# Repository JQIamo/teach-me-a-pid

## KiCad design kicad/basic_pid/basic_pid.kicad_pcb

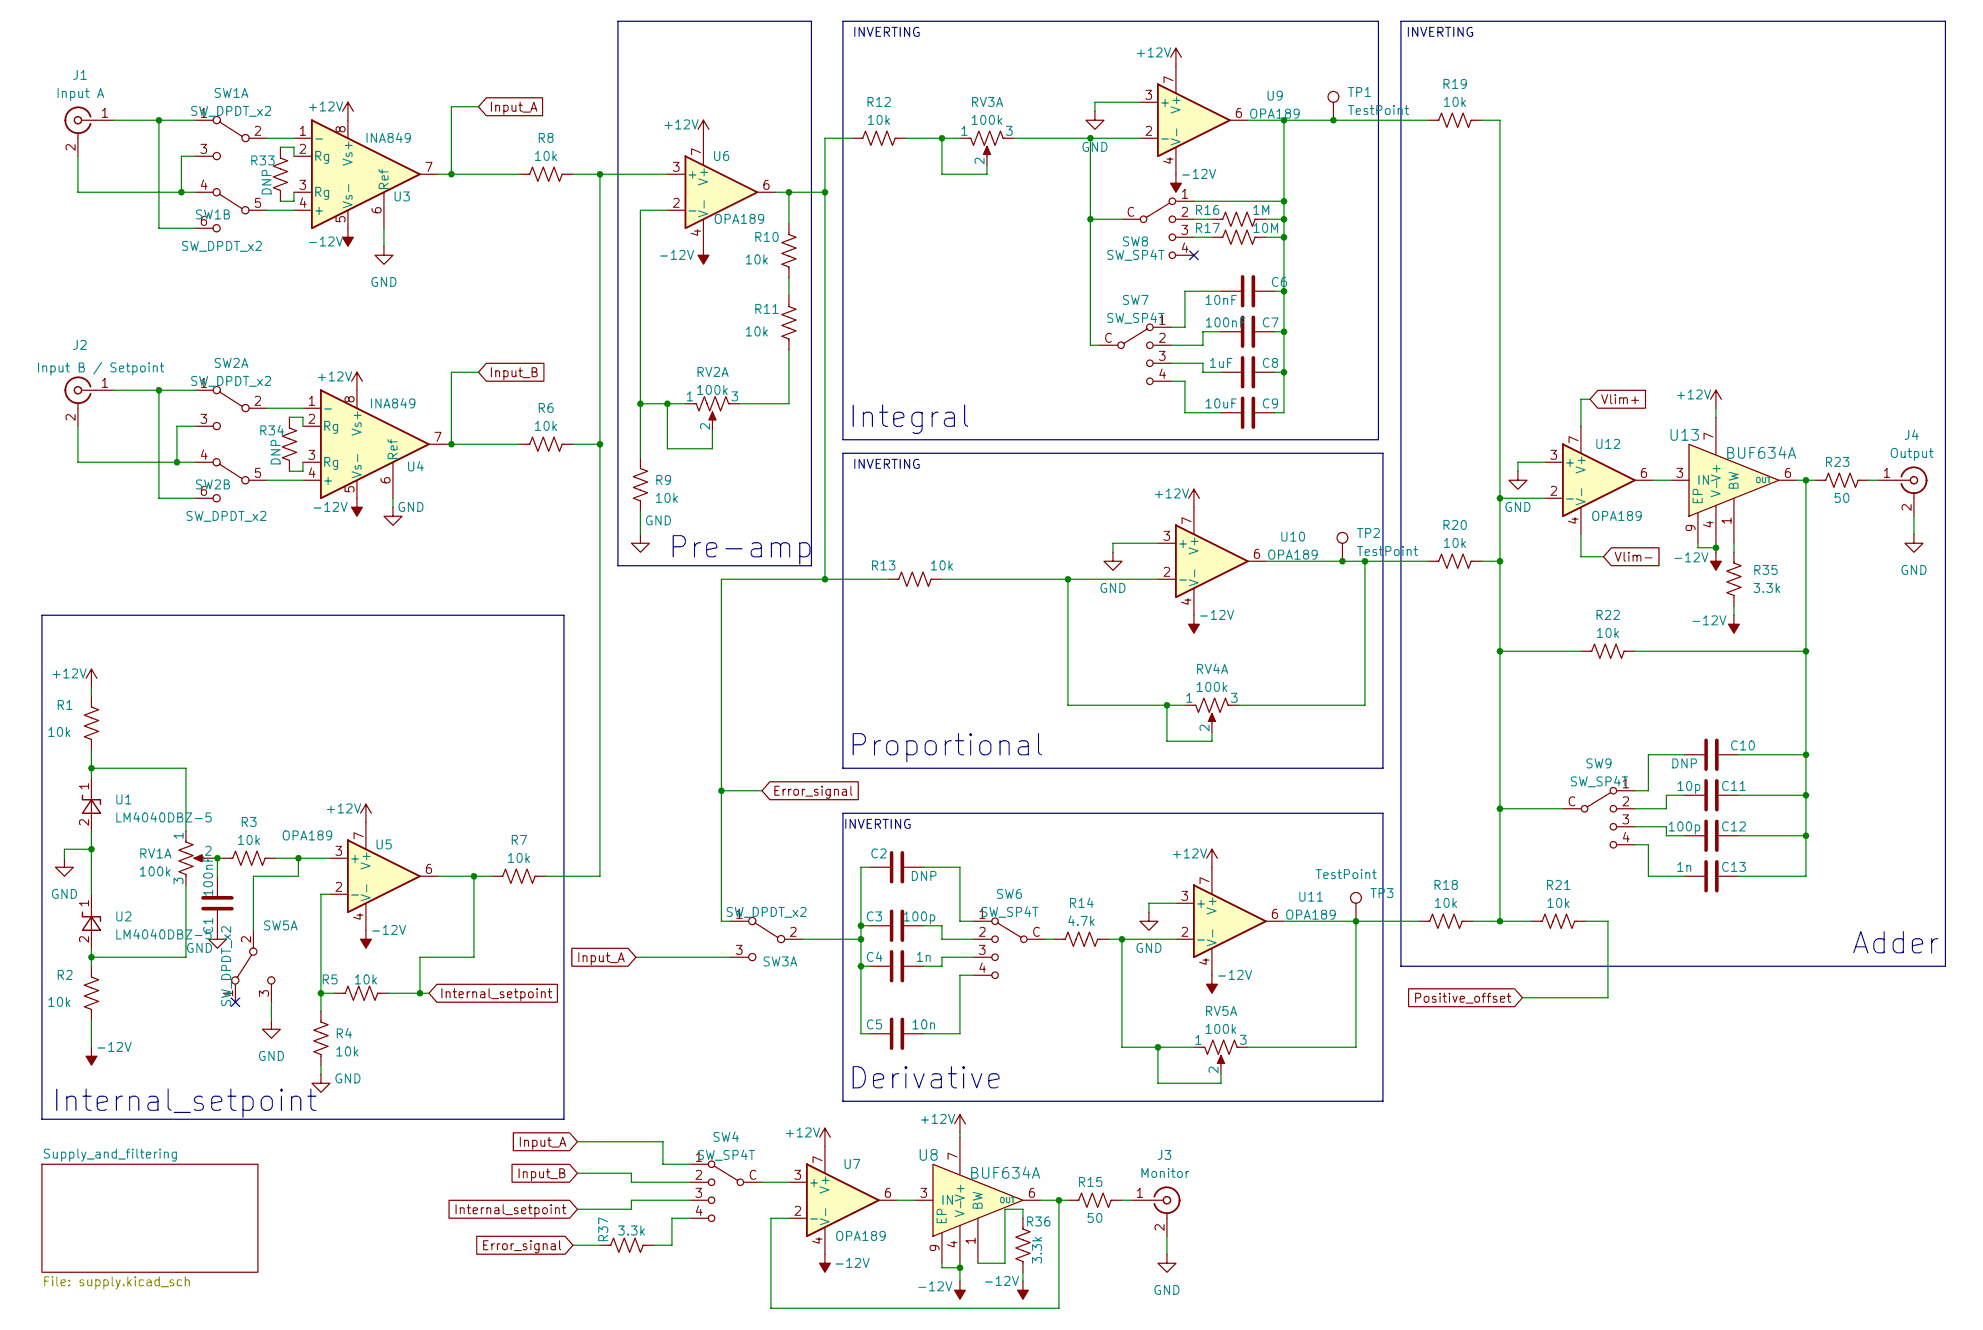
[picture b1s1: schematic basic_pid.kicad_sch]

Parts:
C1, C7: 100nF; C_0805_2012Metric
C2, C10: DNP; C_0805_2012Metric
C3, C12: 100p; C_0805_2012Metric
C4, C13: 1n; C_0805_2012Metric
C5: 10n; C_0805_2012Metric
C6: 10nF; C_0805_2012Metric
C8: 1uF; C_0805_2012Metric
C9: 10uF; C_0805_2012Metric
C11: 10p; C_0805_2012Metric
J1: Input A; BNC_Amphenol_031-5539_Vertical
J2: Input B / Setpoint; BNC_Amphenol_031-5539_Vertical
J3: Monitor; BNC_Amphenol_031-5539_Vertical
J4: Output; BNC_Amphenol_031-5539_Vertical
R1, R2: 10k; R_0805_2012Metric
R3, R4, R5, R6, R7, R8, R9, R10, R11, R12, R13, R18, R19, R20, R21, R22: 10k; R_0805_2012Metric; DIGIKEY 2019-RN73H2ATTD1002B25CT-ND
R14: 4.7k; R_0805_2012Metric
R15, R23: 50; R_0805_2012Metric
R16: 1M; R_0805_2012Metric; PARTNO AC0805JR-071ML; DIGIKEY YAG3766CT-ND
R17: 10M; R_0805_2012Metric; PARTNO RC0805JR-0710ML; DIGIKEY 311-10MARCT-ND
R33, R34: DNP; R_0805_2012Metric; DIGIKEY 2019-RN73H2ATTD1002B25CT-ND
R35, R36, R37: 3.3k; R_0805_2012Metric; DIGIKEY 2019-RN73H2ATTD3301B25CT-ND
RV1, RV2, RV3, RV4, RV5: 100k; Slide_pot_45mm; PARTNO PTL45-15O0-104B1; DIGIKEY PTL45-15O0-104B1-ND
SW1, SW2, SW3, SW5: SW_DPDT_x2; MHS222; PARTNO 1825289-1; DIGIKEY 450-1572-ND
SW4, SW6, SW7, SW8, SW9: SW_SP4T; SLB1470; PARTNO SLB1470; DIGIKEY 679-2621-ND
TP1, TP2, TP3: TestPoint; TestPoint_Pad_D3.0mm
U1, U2: LM4040DBZ-5; SOT-23; PARTNO LM4040B50FTA; DIGIKEY LM4040B50FTADICT-ND
U3, U4: INA849; SOIC-8_3.9x4.9mm_P1.27mm; PARTNO INA849DR‎; DIGIKEY 296-INA849DRCT-ND‎
U5, U6, U7, U9, U10, U11, U12: OPA189; SOIC-8_3.9x4.9mm_P1.27mm; PARTNO OPA189ID; DIGIKEY 296-47522-ND
U8, U13: BUF634A; TI_SO-PowerPAD-8_ThermalVias; PARTNO BUF634AIDDAR; DIGIKEY 296-BUF634AIDDARCT-ND

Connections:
+12V: R1.2, U3.8 (Vs+), U4.8 (Vs+), U5.7 (V+), U6.7 (V+), U7.7 (V+), U8.7 (V+), U9.7 (V+), U10.7 (V+), U11.7 (V+), U13.7 (V+); also elsewhere on the board
-12V: R2.1, R35.1, R36.1, U3.5 (Vs-), U4.5 (Vs-), U5.4 (V-), U6.4 (V-), U7.4 (V-), U8.4 (V-), U8.9 (EP), U9.4 (V-), U10.4 (V-), U11.4 (V-), U13.4 (V-), U13.9 (EP); also elsewhere on the board
Error_signal: R10.2, R12.1, R13.1, R37.2, SW3.1 (A), U6.6
GND: C1.1, J3.2 (Ext), J4.2 (Ext), R4.1, R9.1, SW5.3 (C), U1.2 (A), U2.1 (K), U3.6 (Ref), U4.6 (Ref), U9.3 (+), U10.3 (+), U11.3 (+), U12.3 (+); also elsewhere on the board
Input_A: R8.1, SW3.3 (C), SW4.1, U3.7
Input_B: R6.1, SW4.2, U4.7
Internal_setpoint: R5.2, R7.1, SW4.3, U5.6
unnamed: C1.2, R3.1, RV1.2
unnamed: C2.2, SW6.1
unnamed: C3.2, SW6.2
unnamed: C4.2, SW6.3
unnamed: C5.2, SW6.4
unnamed: C6.1, C7.1, C8.1, C9.1, R16.2, R17.2, R19.1, SW8.1, TP1.1, U9.6
unnamed: C6.2, SW7.1
unnamed: C7.2, SW7.2
unnamed: C8.2, SW7.3
unnamed: C9.2, SW7.4
unnamed: C10.2, SW9.1
unnamed: C11.2, SW9.2
unnamed: C12.2, SW9.3
unnamed: C13.2, SW9.4
unnamed: J1.2 (Ext), SW1.3 (C), SW1.4 (A)
unnamed: J1.1 (In), SW1.1 (A), SW1.6 (C)
unnamed: J2.2 (Ext), SW2.3 (C), SW2.4 (A)
unnamed: J2.1 (In), SW2.1 (A), SW2.6 (C)
unnamed: J3.1 (In), R15.2
unnamed: J4.1 (In), R23.2
unnamed: R10.1, R11.2
unnamed: R11.1, RV2.3
unnamed: R12.2, RV3.1, RV3.2
unnamed: R16.1, SW8.2
unnamed: R17.1, SW8.3
unnamed: R18.1, RV5.3, TP3.1, U11.6
unnamed: R20.1, RV4.3, TP2.1, U10.6
unnamed: R33.1, U3.3 (Rg)
unnamed: R33.2, U3.2 (Rg)
unnamed: R34.1, U4.3 (Rg)
unnamed: R34.2, U4.2 (Rg)
unnamed: R37.1, SW4.4
unnamed: SW1.2 (B), U3.1 (-)
unnamed: SW1.5 (B), U3.4 (+)
unnamed: SW2.2 (B), U4.1 (-)
unnamed: SW2.5 (B), U4.4 (+)
unnamed: C2.1, C3.1, C4.1, C5.1, SW3.2 (B)
unnamed: SW4.C (Common), U7.3 (+)
unnamed: R3.2, SW5.2 (B), U5.3 (+)
unnamed: R14.1, SW6.C (Common)
unnamed: RV3.3, SW7.C (Common), SW8.C (Common), U9.2 (-)
unnamed: R18.2, R19.2, R20.2, R21.1, R22.1, SW9.C (Common), U12.2 (-)
unnamed: R1.1, RV1.1, U1.1 (K)
unnamed: R2.2, RV1.3, U2.2 (A)
unnamed: R4.2, R5.1, U5.2 (-)
unnamed: R6.2, R7.2, R8.2, U6.3 (+)
unnamed: R9.2, RV2.1, RV2.2, U6.2 (-)
unnamed: R15.1, U7.2 (-), U8.6 (OUT)
unnamed: R36.2, U8.1 (BW)
unnamed: U7.6, U8.3 (IN)
unnamed: R13.2, RV4.1, RV4.2, U10.2 (-)
unnamed: R14.2, RV5.1, RV5.2, U11.2 (-)
unnamed: R35.2, U13.1 (BW)
unnamed: U12.6, U13.3 (IN)
unnamed: C10.1, C11.1, C12.1, C13.1, R22.2, R23.1, U13.6 (OUT)
Positive_offset: R21.2; also elsewhere on the board
Vlim+: U12.7 (V+); also elsewhere on the board
Vlim-: U12.4 (V-); also elsewhere on the board

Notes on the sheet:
INVERTING
Pre-amp
Proportional
Adder
Derivative
Integral
Internal_setpoint

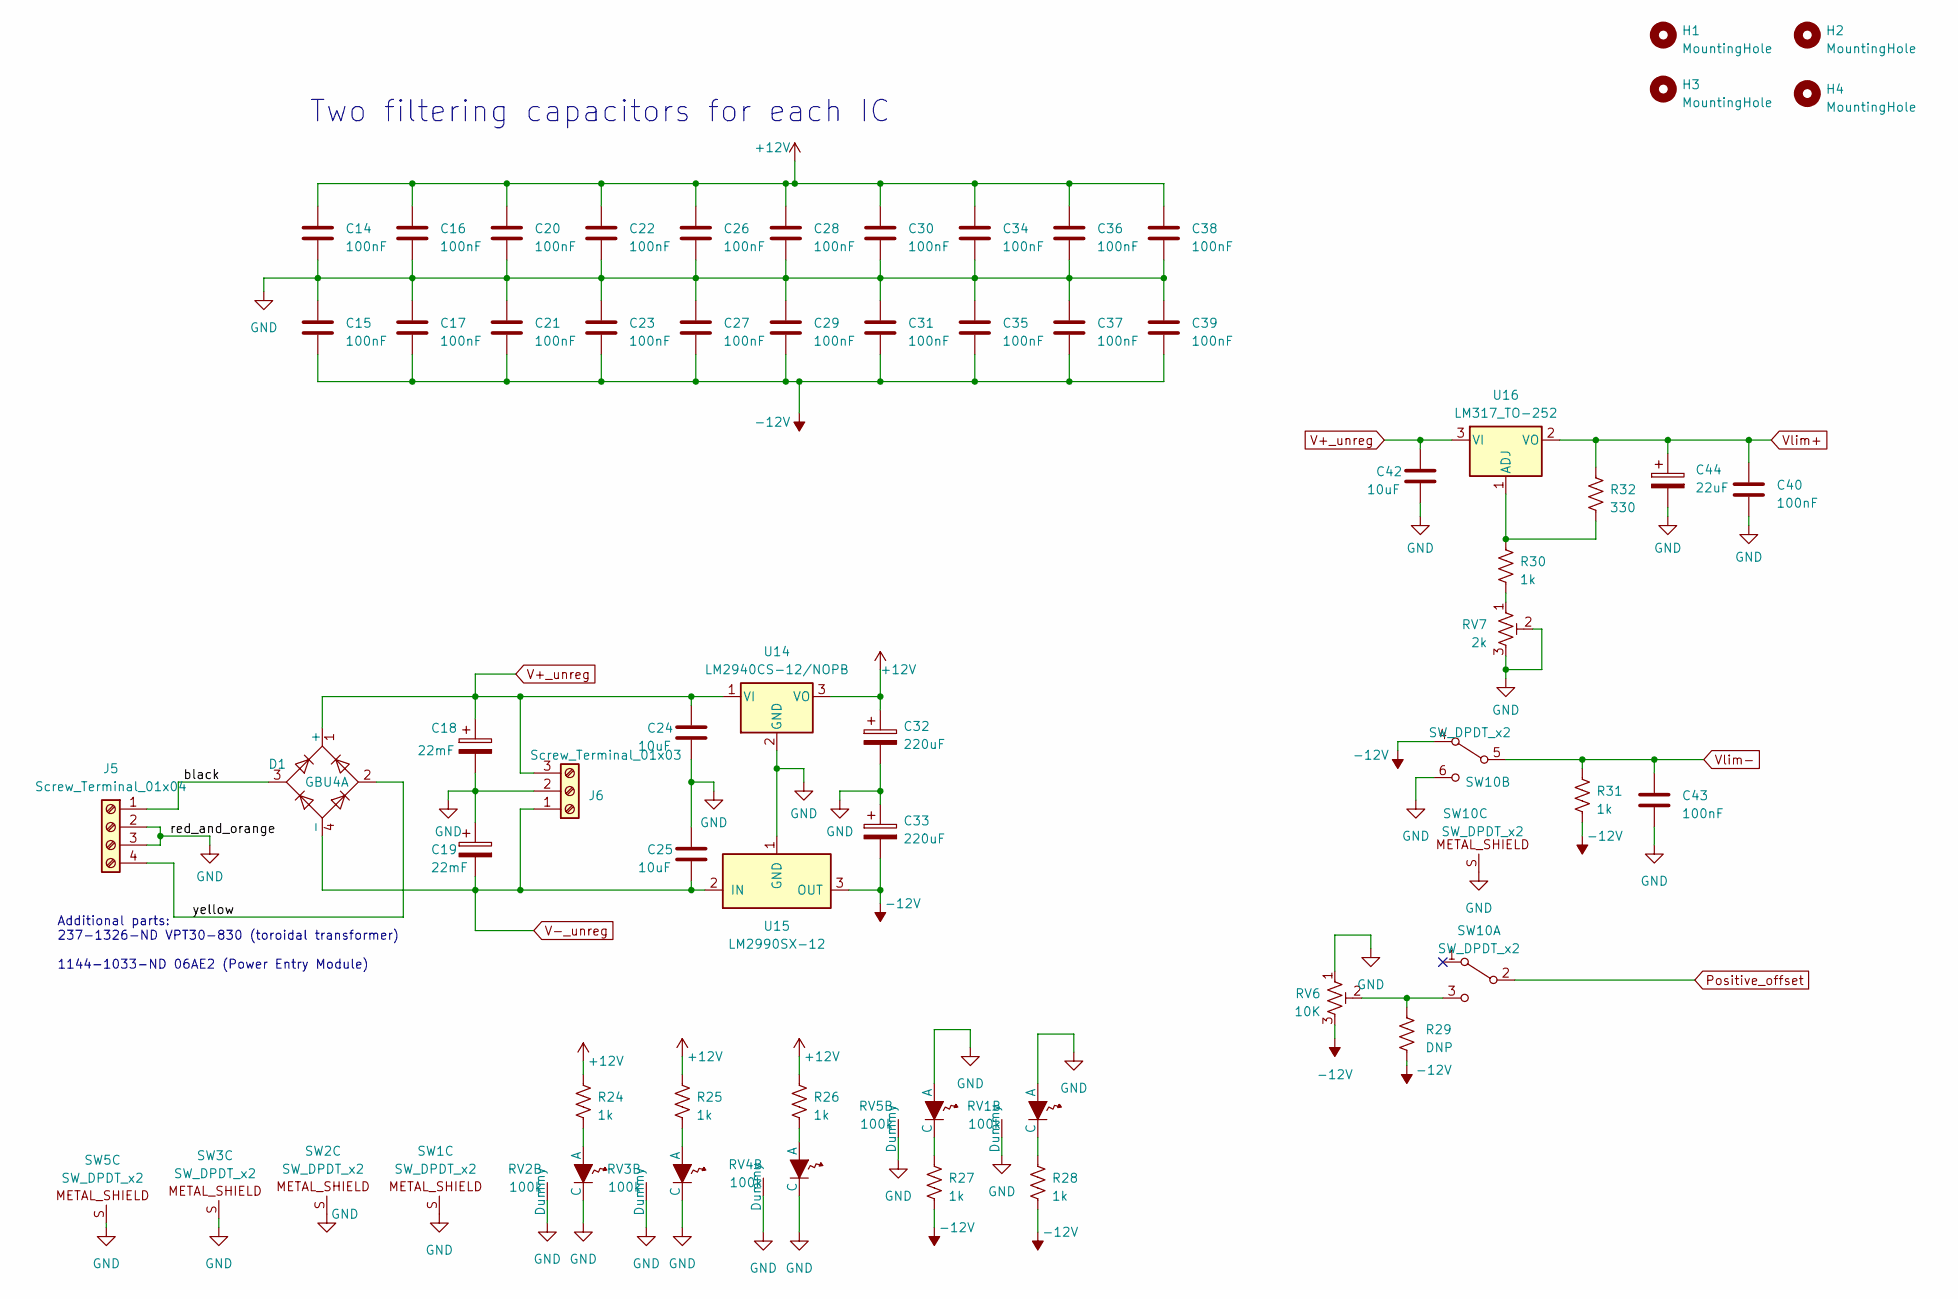
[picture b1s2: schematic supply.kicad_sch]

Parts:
C14, C15, C16, C17, C20, C21, C22, C23, C26, C27, C28, C29, C30, C31, C34, C35, C36, C37, C38, C39, C40, C43: 100nF; C_0805_2012Metric
C18, C19: 22mF; CP_Radial_D30.0mm_P10.00mm_SnapIn; PARTNO 380LX223M035K052; DIGIKEY 338-2433-ND
C24, C25, C42: 10uF; C_1210_3225Metric
C32, C33: 220uF; CP_Elec_8x6.9; PARTNO EEE-1VA221UP; DIGIKEY PCE3955CT-ND
C44: 22uF; CP_Elec_4x5.8; PARTNO UCM1V220MCL1GS; DIGIKEY 493-14929-1-ND
D1: GBU4A; Diode_Bridge_Vishay_GBU; PARTNO GBU4A; DIGIKEY GBU4A-ND
H1, H2, H3, H4: MountingHole; MountingHole_3.2mm_M3_ISO14580
J5: Screw_Terminal_01x04; TerminalBlock_Altech_AK300-4_P5.00mm
J6: Screw_Terminal_01x03; TerminalBlock_Altech_AK300-3_P5.00mm
R24, R25, R26, R27, R28, R30, R31: 1k; R_0805_2012Metric
R29: DNP; R_0805_2012Metric
R32: 330; R_0805_2012Metric
RV1, RV2, RV3, RV4, RV5: 100k; Slide_pot_45mm; PARTNO PTL45-15O0-104B1; DIGIKEY PTL45-15O0-104B1-ND
RV6: 10K; Potentiometer_Bourns_3296W_Vertical; PARTNO 3296W-1-103RLF; DIGIKEY 118-3296W-1-103RLFCT-ND
RV7: 2k; Potentiometer_Bourns_3296W_Vertical; PARTNO M64W202KB40; DIGIKEY SP064W-2.0K-ND
SW1, SW2, SW3, SW5, SW10: SW_DPDT_x2; MHS222; PARTNO 1825289-1; DIGIKEY 450-1572-ND
U14: LM2940CS-12/NOPB; TO-263-3_TabPin2; PARTNO LM2940CS-12/NOPB; DIGIKEY LM2940CS-12/NOPB-ND
U15: LM2990SX-12; TO-263-3_TabPin2; PARTNO LM2990SX-12/NOPB; DIGIKEY LM2990SX-12/NOPBCT-ND
U16: LM317_TO-252; TO-252-2; PARTNO LM317MDT-TR; DIGIKEY 497-1574-1-ND

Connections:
+12V: C14.1, C16.1, C20.1, C22.1, C26.1, C28.1, C30.1, C32.1, C34.1, C36.1, C38.1, R24.2, R25.2, R26.2, U14.3 (VO); also elsewhere on the board
-12V: C15.2, C17.2, C21.2, C23.2, C27.2, C29.2, C31.2, C33.2, C35.2, C37.2, C39.2, R27.1, R28.1, R29.1, R31.1, RV6.3, SW10.4 (A), U15.3 (OUT); also elsewhere on the board
/Supply_and_filtering/black: D1.3, J5.1
/Supply_and_filtering/yellow: D1.2, J5.4
GND: C14.2, C15.1, C16.2, C17.1, C18.2, C19.1, C20.2, C21.1, C22.2, C23.1, C24.2, C25.1, C26.2, C27.1, C28.2, C29.1, C30.2, C31.1, C32.2, C33.1, C34.2, C35.1, C36.2, C37.1, C38.2, C39.1, C40.2, C42.2, C43.2, C44.2, J5.2, J5.3, J6.2, RV1.A, RV1.L (Dummy), RV2.C, RV2.L (Dummy), RV3.C, RV3.L (Dummy), RV4.C, RV4.L (Dummy), RV5.A, RV5.L (Dummy), RV6.1, RV7.2, RV7.3, SW1.S, SW2.S, SW3.S, SW5.S, SW10.6 (C), SW10.S, U14.2 (GND), U15.1 (GND); also elsewhere on the board
unnamed: R24.1, RV2.A
unnamed: R25.1, RV3.A
unnamed: R26.1, RV4.A
unnamed: R27.2, RV5.C
unnamed: R28.2, RV1.C
unnamed: R30.1, RV7.1
unnamed: R29.2, RV6.2, SW10.3 (C)
unnamed: R30.2, R32.1, U16.1 (ADJ)
Positive_offset: SW10.2 (B); also elsewhere on the board
V+_unreg: C18.1, C24.1, C42.1, D1.1 (+), J6.3, U14.1 (VI), U16.3 (VI)
V-_unreg: C19.2, C25.2, D1.4 (-), J6.1, U15.2 (IN)
Vlim+: C40.1, C44.1, R32.2, U16.2 (VO); also elsewhere on the board
Vlim-: C43.1, R31.2, SW10.5 (B); also elsewhere on the board

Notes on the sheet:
Two filtering capacitors for each IC
Additional parts: 237-1326-ND VPT30-830 (toroidal transformer) 1144-1033-ND 06AE2 (Power Entry Module)

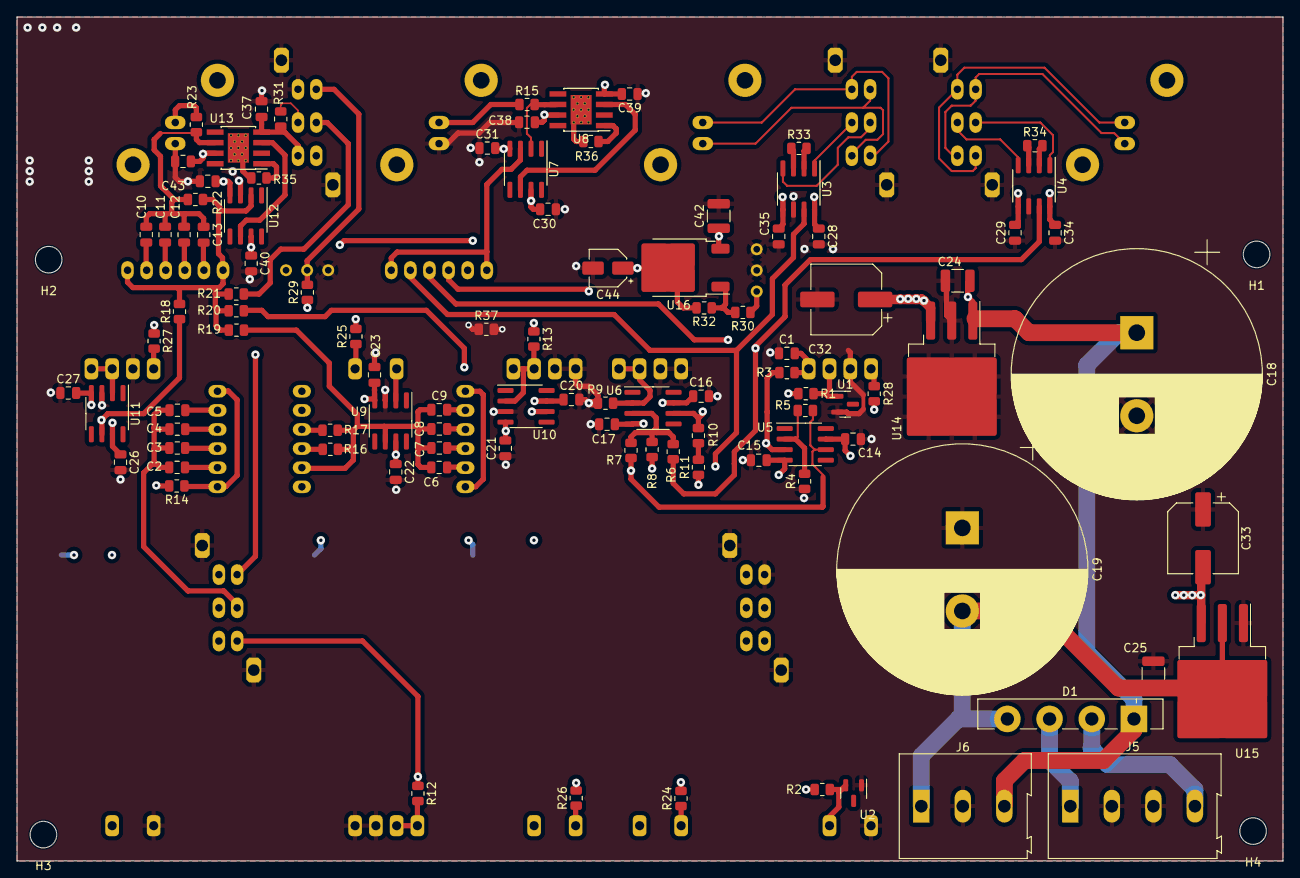
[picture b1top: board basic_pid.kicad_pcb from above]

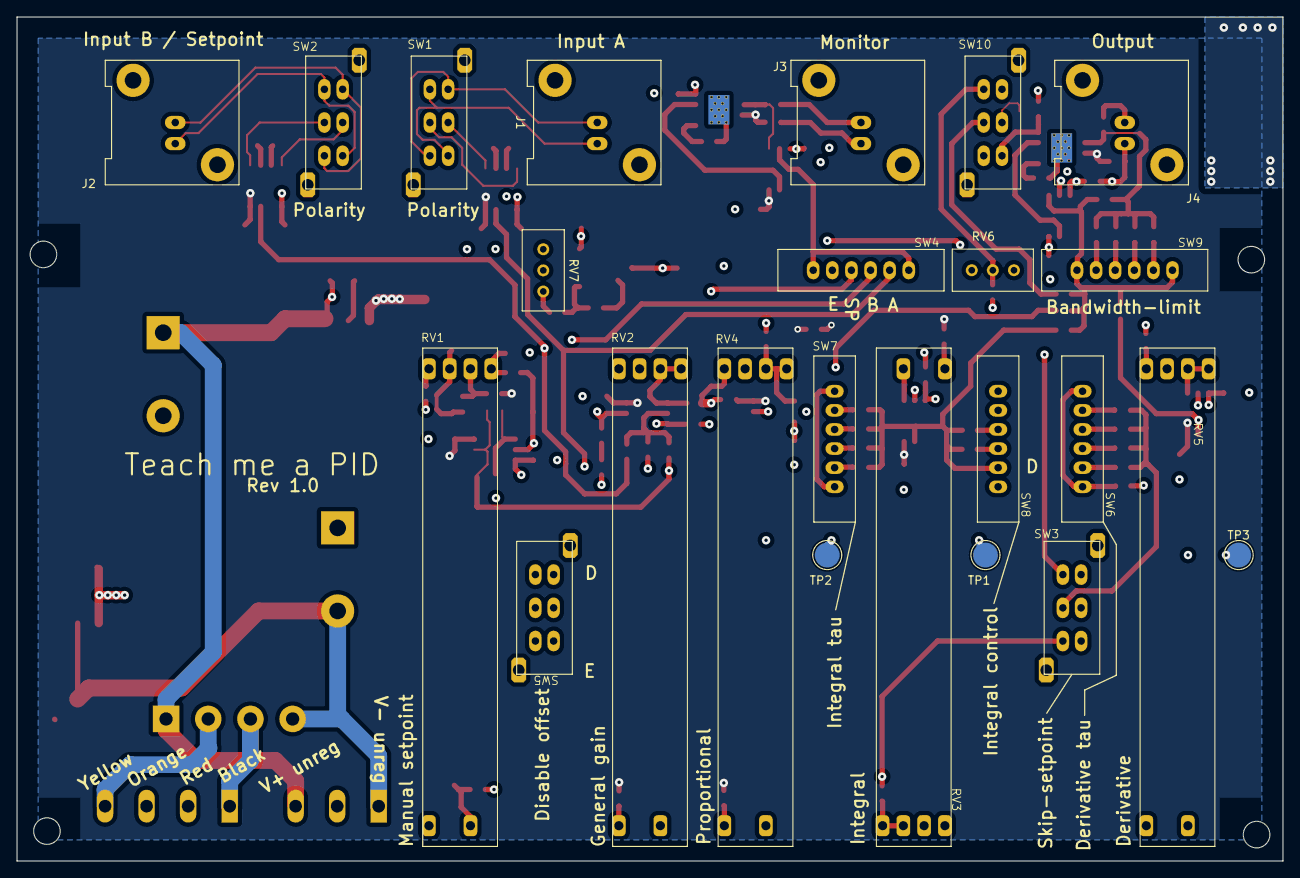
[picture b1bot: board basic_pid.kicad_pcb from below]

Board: 4 copper layers, 152.4 x 101.6 mm, 127 parts (24 on the bottom side), 77 nets.

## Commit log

2023-07-06 This contains ideas for a high-speed design
2023-10-30 Fixed wrong part and added shunt resistor values
2024-07-03 Fixed monitor instability
    Added a 3.3 kOhm resistor on each output buffer's bandwith control pin
    to increase the bandwidth from 30 MHz to 90 MHz.
    This should prevent oscillations and instabilities we noticed while
    testing the PID
2024-07-26 Not sure if it works: Just a possibile fix for a noisy monitor when sampling error signal
